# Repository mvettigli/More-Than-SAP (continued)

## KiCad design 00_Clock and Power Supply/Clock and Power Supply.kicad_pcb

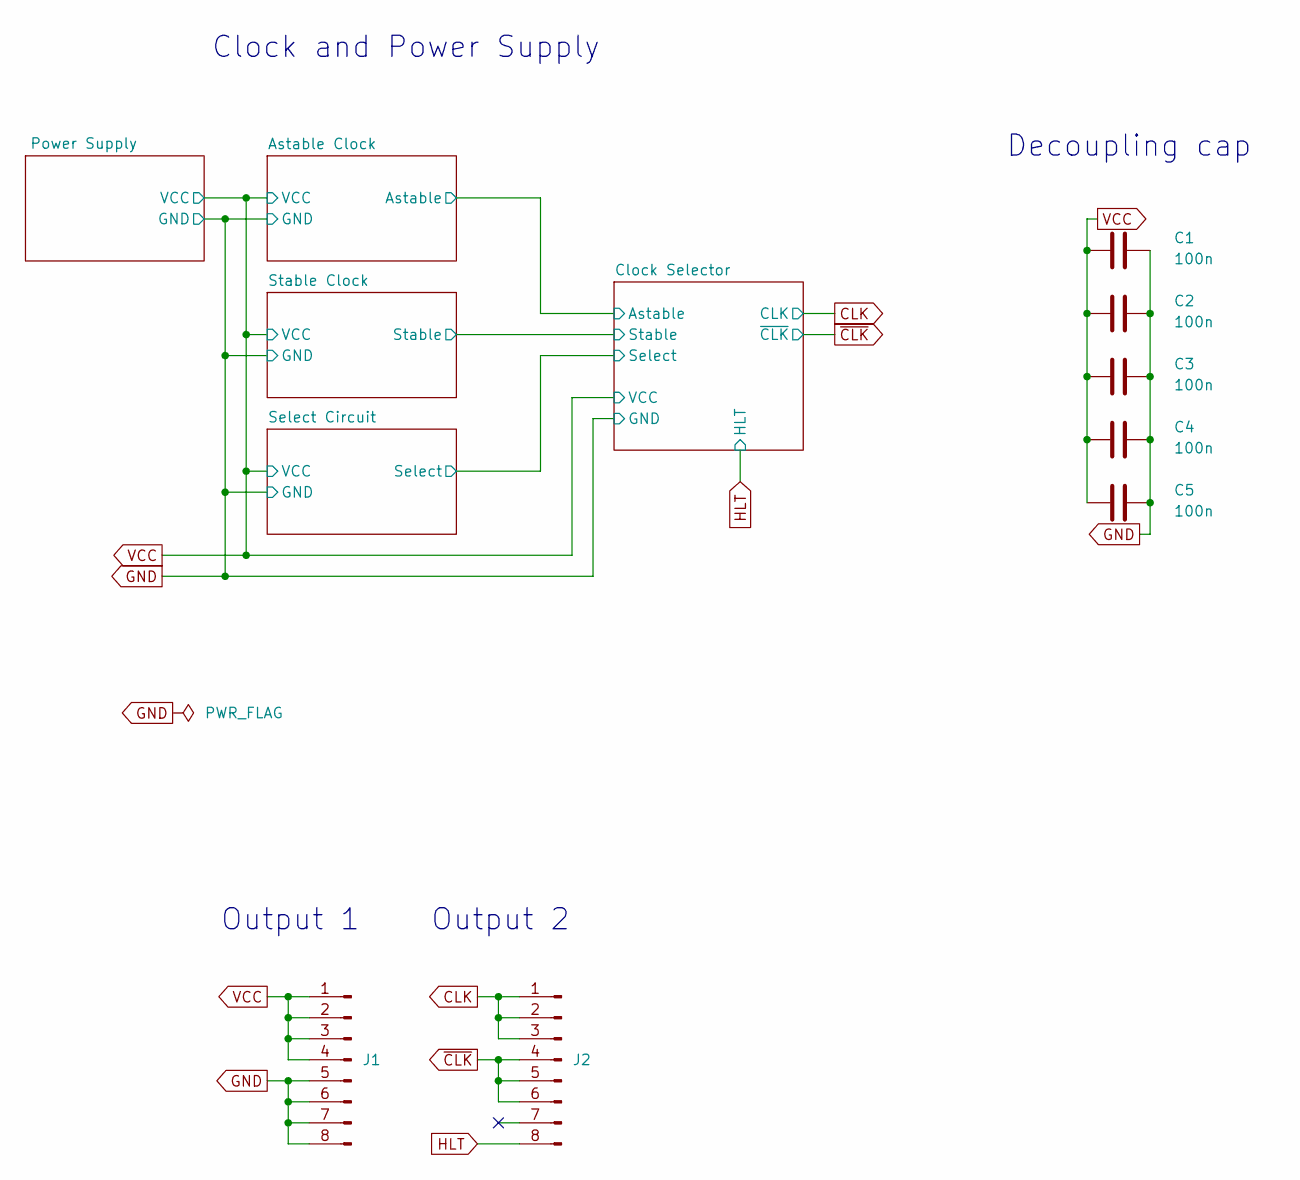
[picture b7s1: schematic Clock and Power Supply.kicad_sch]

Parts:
C1, C2, C3, C4, C5: 100n; C_Disc_D3.0mm_W1.6mm_P2.50mm
J1: Output 1; PinHeader_1x08_P2.54mm_Horizontal
J2: Output 2; PinHeader_1x08_P2.54mm_Horizontal

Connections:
CLK: J2.1, J2.2, J2.3; also elsewhere on the board
GND: C1.2, C2.2, C3.2, C4.2, C5.2, J1.5, J1.6, J1.7, J1.8; also elsewhere on the board
HLT: J2.8; also elsewhere on the board
VCC: C1.1, C2.1, C3.1, C4.1, C5.1, J1.1, J1.2, J1.3, J1.4; also elsewhere on the board
~CLK: J2.4, J2.5, J2.6; also elsewhere on the board

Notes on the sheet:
Clock and Power Supply
Output 2
Output 1
Decoupling cap

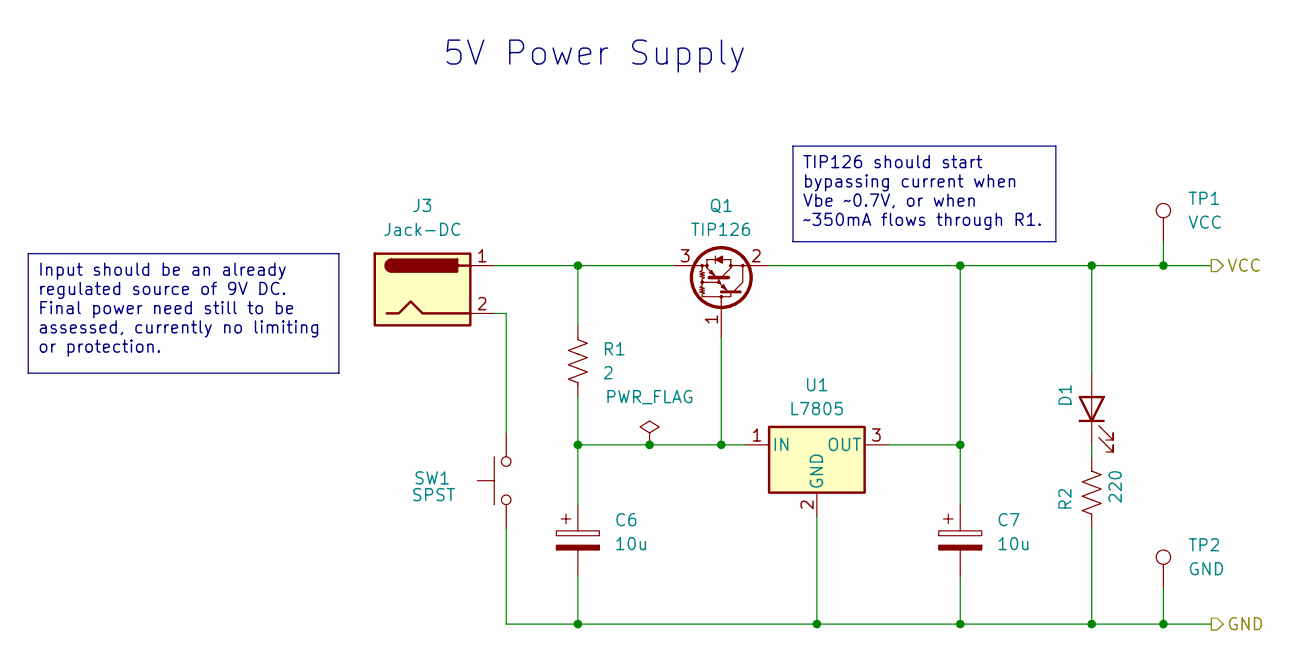
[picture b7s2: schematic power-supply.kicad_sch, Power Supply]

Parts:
C6, C7: 10u; CP_Radial_D5.0mm_P2.50mm
D1: RED; LED_D5.0mm
J3: Jack-DC; BarrelJack_Horizontal
Q1: TIP126; TO-220-3_Vertical
R1: 2; R_Box_L14.0mm_W5.0mm_P9.00mm
R2: 220; R_Axial_DIN0207_L6.3mm_D2.5mm_P10.16mm_Horizontal
SW1: SPST; SW-TH_G-SWITCH-PS-22F03N
TP1: VCC; TestPoint_Loop_D3.50mm_Drill0.9mm_Beaded
TP2: GND; TestPoint_Loop_D3.50mm_Drill0.9mm_Beaded
U1: L7805; TO-220-3_Vertical

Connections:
GND: C6.2, C7.2, R2.2, SW1.1, TP2.1, U1.2 (GND); also elsewhere on the board
unnamed: D1.1 (K), R2.1
unnamed: J3.2, SW1.2
unnamed: C6.1, Q1.1 (B), R1.2, U1.1 (IN)
unnamed: J3.1, Q1.3 (E), R1.1
VCC: C7.1, D1.2 (A), Q1.2 (C), TP1.1, U1.3 (OUT); also elsewhere on the board

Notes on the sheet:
5V Power Supply
TIP126 should start bypassing current when Vbe ~0.7V, or when ~350mA flows through R1.
Input should be an already regulated source of 9V DC. Final power need still to be assessed, currently no limiting or protection.

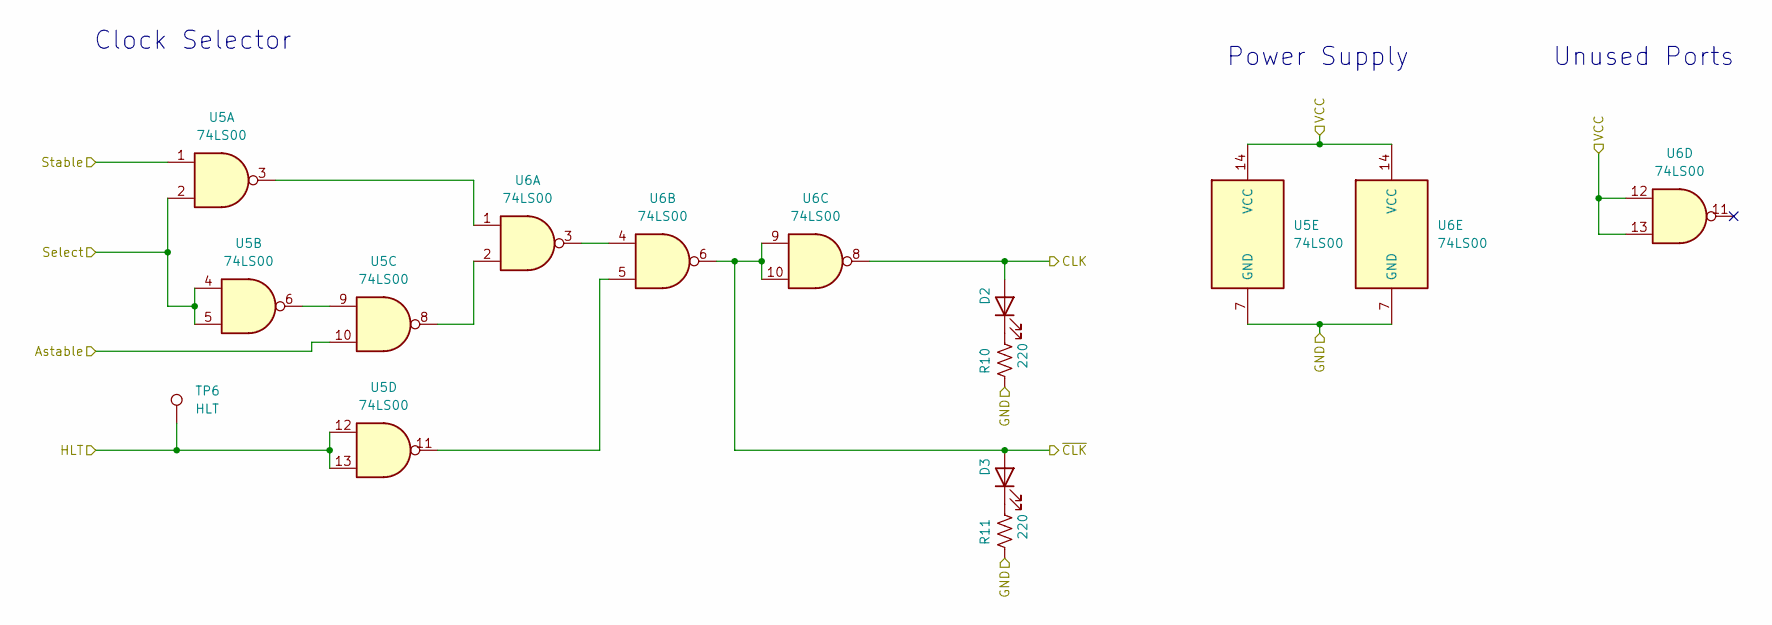
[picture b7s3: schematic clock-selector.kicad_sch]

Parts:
D2, D3: BLUE; LED_D5.0mm
R10, R11: 220; R_Axial_DIN0207_L6.3mm_D2.5mm_P10.16mm_Horizontal
TP6: HLT; TestPoint_Loop_D3.50mm_Drill0.9mm_Beaded
U5, U6: 74LS00; DIP-14_W7.62mm

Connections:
/Astable Clock/Astable: U5.10; also elsewhere on the board
/Clock Selector/Select: U5.2, U5.4, U5.5; also elsewhere on the board
/Clock Selector/Stable: U5.1; also elsewhere on the board
CLK: D2.2 (A), U6.8; also elsewhere on the board
GND: R10.2, R11.2, U5.7 (GND), U6.7 (GND); also elsewhere on the board
HLT: TP6.1, U5.12, U5.13; also elsewhere on the board
unnamed: D2.1 (K), R10.1
unnamed: D3.1 (K), R11.1
unnamed: U5.3, U6.1
unnamed: U5.6, U5.9
unnamed: U5.8, U6.2
unnamed: U5.11, U6.5
unnamed: U6.3, U6.4
VCC: U5.14 (VCC), U6.12, U6.13, U6.14 (VCC); also elsewhere on the board
~CLK: D3.2 (A), U6.6, U6.9, U6.10; also elsewhere on the board

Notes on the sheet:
Power Supply
Unused Ports
Clock Selector

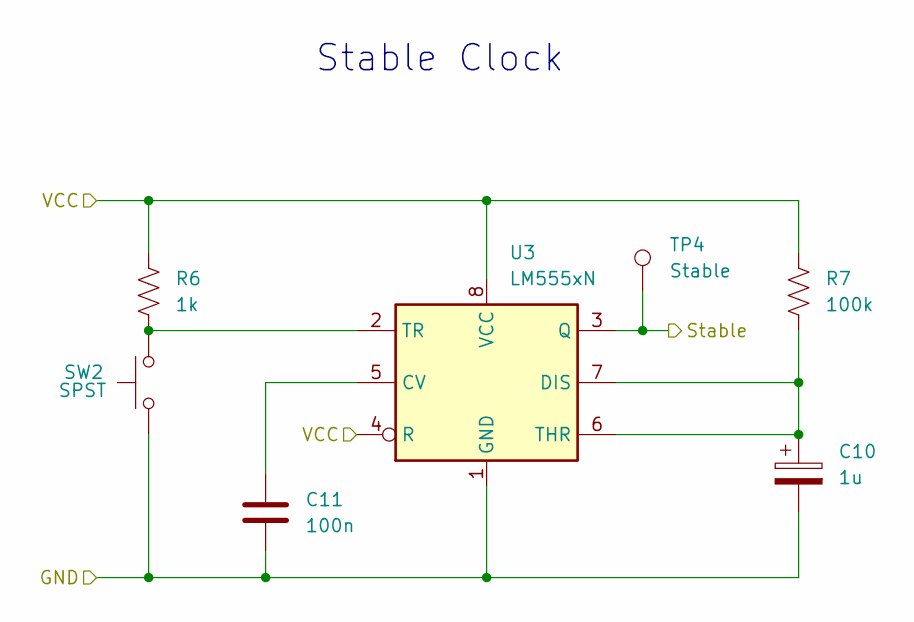
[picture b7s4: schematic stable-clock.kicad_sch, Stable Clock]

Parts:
C10: 1u; CP_Radial_D5.0mm_P2.50mm
C11: 100n; C_Disc_D3.0mm_W1.6mm_P2.50mm
R6: 1k; R_Axial_DIN0207_L6.3mm_D2.5mm_P10.16mm_Horizontal
R7: 100k; R_Axial_DIN0207_L6.3mm_D2.5mm_P10.16mm_Horizontal
SW2: SPST; SW-TH_G-SWITCH-PS-22F03N
TP4: Stable; TestPoint_Loop_D3.50mm_Drill0.9mm_Beaded
U3: LM555xN; DIP-8_W7.62mm

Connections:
/Clock Selector/Stable: TP4.1, U3.3 (Q); also elsewhere on the board
GND: C10.2, C11.2, SW2.1, U3.1 (GND); also elsewhere on the board
unnamed: C11.1, U3.5 (CV)
unnamed: C10.1, R7.1, U3.6 (THR), U3.7 (DIS)
unnamed: R6.1, SW2.2, U3.2 (TR)
VCC: R6.2, R7.2, U3.4 (R), U3.8 (VCC); also elsewhere on the board

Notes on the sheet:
Stable Clock

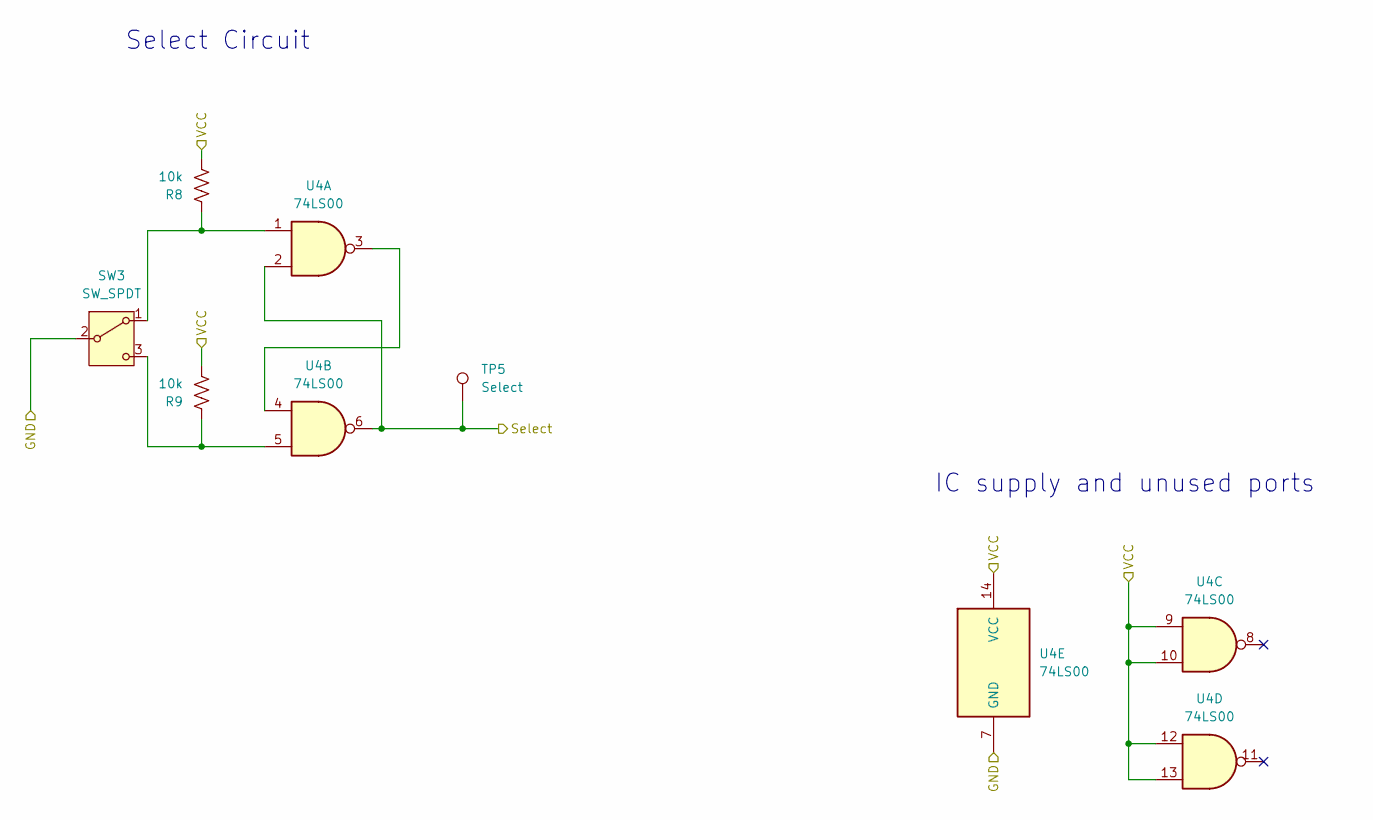
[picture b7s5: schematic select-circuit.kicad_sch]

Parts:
R8, R9: 10k; R_Axial_DIN0207_L6.3mm_D2.5mm_P10.16mm_Horizontal
SW3: SW_SPDT; SW-TH_G-SWITCH-PS-22F03N
TP5: Select; TestPoint_Loop_D3.50mm_Drill0.9mm_Beaded
U4: 74LS00; DIP-14_W7.62mm

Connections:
/Clock Selector/Select: TP5.1, U4.2, U4.6; also elsewhere on the board
GND: SW3.2 (B), U4.7 (GND); also elsewhere on the board
unnamed: R8.1, SW3.1 (A), U4.1
unnamed: R9.1, SW3.3 (C), U4.5
unnamed: U4.3, U4.4
VCC: R8.2, R9.2, U4.9, U4.10, U4.12, U4.13, U4.14 (VCC); also elsewhere on the board

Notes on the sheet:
Select Circuit
IC supply and unused ports

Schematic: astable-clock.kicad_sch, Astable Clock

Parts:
C8: 1u; CP_Radial_D5.0mm_P2.50mm
C9: 100n; C_Disc_D3.0mm_W1.6mm_P2.50mm
R3, R5: 1k; R_Axial_DIN0207_L6.3mm_D2.5mm_P10.16mm_Horizontal
R4: 1M; Potentiometer_Alps_RK09K_Single_Horizontal
TP3: Astable; TestPoint_Loop_D3.50mm_Drill0.9mm_Beaded
U2: LM555xN; DIP-8_W7.62mm

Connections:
/Astable Clock/Astable: TP3.1, U2.3 (Q); also elsewhere on the board
GND: C8.2, C9.2, U2.1 (GND); also elsewhere on the board
unnamed: R4.2, R5.2
unnamed: C9.1, U2.5 (CV)
unnamed: R3.1, R4.1, U2.7 (DIS)
unnamed: C8.1, R5.1, U2.2 (TR), U2.6 (THR)
VCC: R3.2, U2.4 (R), U2.8 (VCC); also elsewhere on the board

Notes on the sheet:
Astable Clock

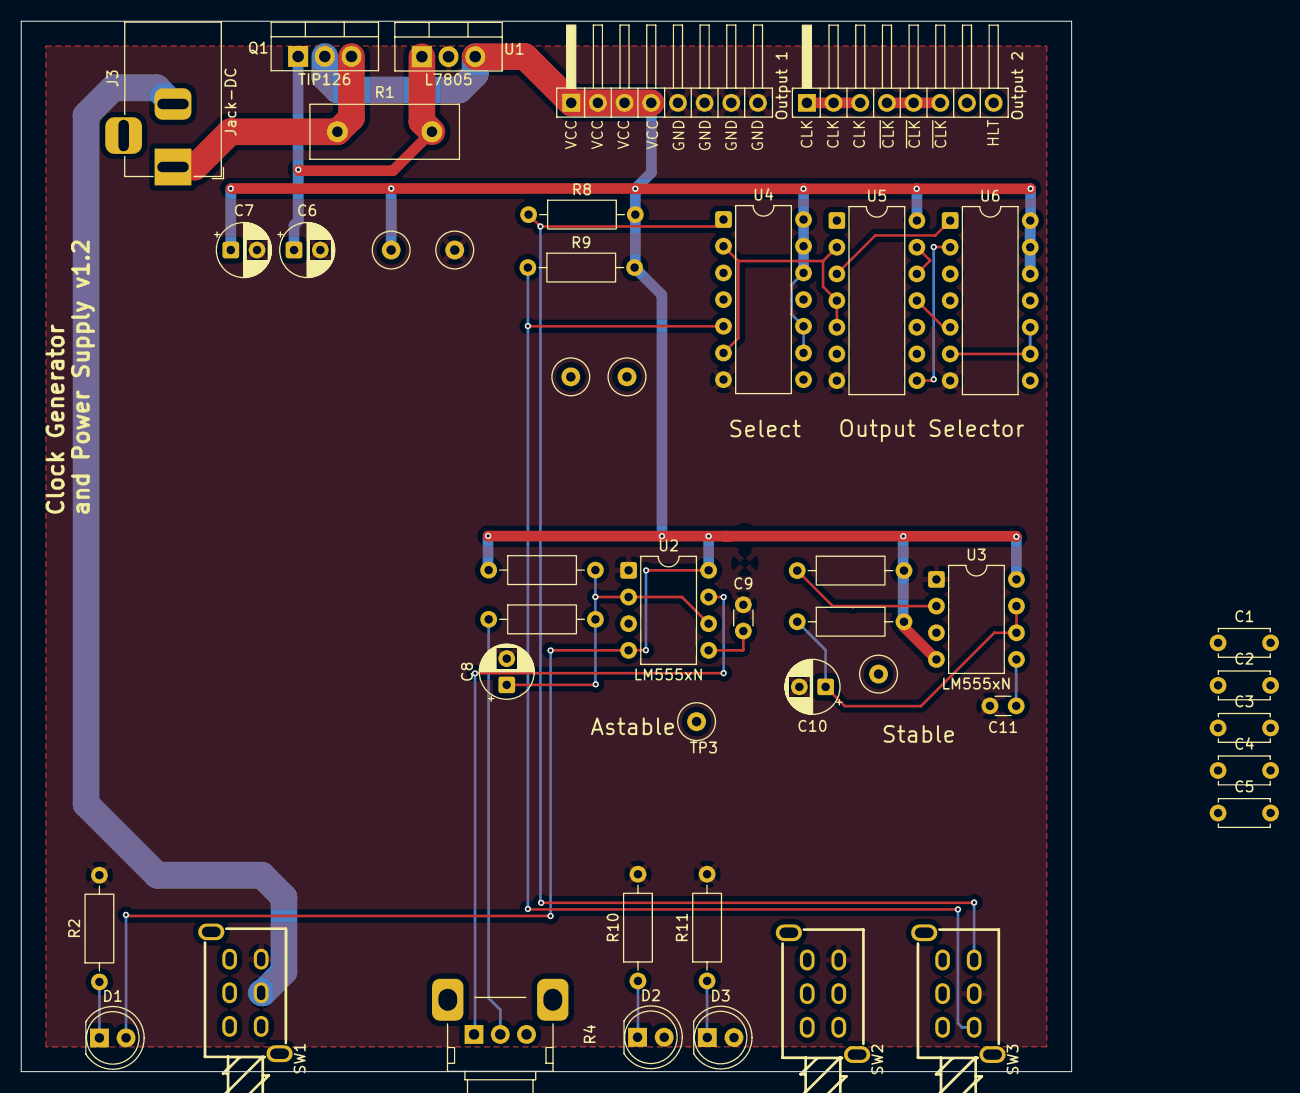
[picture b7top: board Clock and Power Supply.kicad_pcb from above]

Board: 2 copper layers, 100.0 x 100.0 mm, 44 parts (0 on the bottom side), 29 nets.

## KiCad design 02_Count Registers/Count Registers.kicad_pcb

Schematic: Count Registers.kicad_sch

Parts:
C1, C2, C3: 100nF; C_Disc_D4.7mm_W2.5mm_P5.00mm
J1: Data bus; PinHeader_1x08_P2.54mm_Horizontal
J2: Alu-X bus; PinHeader_1x08_P2.54mm_Horizontal
J3: Alu-Y bus; PinHeader_1x08_P2.54mm_Horizontal
J4: Input 1; PinHeader_1x08_P2.54mm_Horizontal
J5: Input 2; PinHeader_1x08_P2.54mm_Horizontal
U1, U3: 74LS08; DIP-14_W7.62mm
U2: 74LS139; DIP-16_W7.62mm

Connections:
/Count register I/U/~D: U1.5, U2.6 (O2); also elsewhere on the board
/Count register I/~CE: U1.6; also elsewhere on the board
/Count register I/~WE: U1.3; also elsewhere on the board
/Count register J/U/~D: U1.10, U2.10 (O2); also elsewhere on the board
/Count register J/~CE: U1.8; also elsewhere on the board
/Count register J/~WE: U1.11; also elsewhere on the board
/Word Selector/~CLR: U3.3; also elsewhere on the board
CLK: J4.2; also elsewhere on the board
D0: J1.1; also elsewhere on the board
D1: J1.2; also elsewhere on the board
D2: J1.3; also elsewhere on the board
D3: J1.4; also elsewhere on the board
D4: J1.5; also elsewhere on the board
D5: J1.6; also elsewhere on the board
D6: J1.7; also elsewhere on the board
D7: J1.8; also elsewhere on the board
GND: C1.2, C2.2, C3.2, J4.8, U1.7 (GND), U2.1 (E), U2.8 (GND), U2.15 (E), U3.4, U3.5, U3.7 (GND), U3.9, U3.10, U3.12, U3.13; also elsewhere on the board
IC0: J4.6, U2.2 (A0)
IC1: J4.7, U2.3 (A1)
JC0: J5.3, U2.14 (A0)
JC1: J5.4, U2.13 (A1)
unnamed: U1.4, U2.5 (O1)
unnamed: U1.2, U2.7 (O3), U3.2
unnamed: U1.9, U2.11 (O1)
unnamed: U1.13, U2.9 (O3), U3.1
VCC: C1.1, C2.1, C3.1, J4.1, U1.14 (VCC), U2.16 (VCC), U3.14 (VCC); also elsewhere on the board
X0: J2.1; also elsewhere on the board
X1: J2.2; also elsewhere on the board
X2: J2.3; also elsewhere on the board
X3: J2.4; also elsewhere on the board
X4: J2.5; also elsewhere on the board
X5: J2.6; also elsewhere on the board
X6: J2.7; also elsewhere on the board
X7: J2.8; also elsewhere on the board
Y0: J3.1; also elsewhere on the board
Y1: J3.2; also elsewhere on the board
Y2: J3.3; also elsewhere on the board
Y3: J3.4; also elsewhere on the board
Y4: J3.5; also elsewhere on the board
Y5: J3.6; also elsewhere on the board
Y6: J3.7; also elsewhere on the board
Y7: J3.8; also elsewhere on the board
~CLK: J4.3
~IRI: J4.5, U1.1
~IRO: J4.4; also elsewhere on the board
~IXO: J5.5; also elsewhere on the board
~IYO: J5.6; also elsewhere on the board
~JRI: J5.2, U1.12
~JRO: J5.1; also elsewhere on the board
~JXO: J5.7; also elsewhere on the board
~JYO: J5.8; also elsewhere on the board

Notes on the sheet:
Alu-X Bus
Data Bus
Input 1
IC Power Supply
Input 2
Decoupling cap
Count Register J
Unsed Ports
ERC
Count Register I
Alu-Y Bus
Two count registers I and J on a same board using the 74LS169 binary counter and 74LS245 for accessing the content to the bus and directly to Alu-X and Alu-Y buses. The up or down clock is selected through 74LS139 decoder and AND ports. A XNOR port should have been used instead of AND but since 2 o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

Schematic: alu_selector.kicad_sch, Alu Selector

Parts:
C10: 10nF; C_Disc_D4.7mm_W2.5mm_P5.00mm
U10: 74LS245; DIP-20_W7.62mm

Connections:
/Alu selector I-X/Q0: U10.2 (A0); also elsewhere on the board
/Alu selector I-X/Q1: U10.3 (A1); also elsewhere on the board
/Alu selector I-X/Q2: U10.4 (A2); also elsewhere on the board
/Alu selector I-X/Q3: U10.5 (A3); also elsewhere on the board
/Alu selector I-X/Q4: U10.6 (A4); also elsewhere on the board
/Alu selector I-X/Q5: U10.7 (A5); also elsewhere on the board
/Alu selector I-X/Q6: U10.8 (A6); also elsewhere on the board
/Alu selector I-X/Q7: U10.9 (A7); also elsewhere on the board
GND: C10.2, U10.10 (GND); also elsewhere on the board
VCC: C10.1, U10.1 (~DIR), U10.20 (VCC); also elsewhere on the board
X0: U10.18 (B0); also elsewhere on the board
X1: U10.17 (B1); also elsewhere on the board
X2: U10.16 (B2); also elsewhere on the board
X3: U10.15 (B3); also elsewhere on the board
X4: U10.14 (B4); also elsewhere on the board
X5: U10.13 (B5); also elsewhere on the board
X6: U10.12 (B6); also elsewhere on the board
X7: U10.11 (B7); also elsewhere on the board
~IXO: U10.19 (~CE); also elsewhere on the board

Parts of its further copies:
C11, C12, C13: 10nF; C_Disc_D4.7mm_W2.5mm_P5.00mm
U11, U12, U13: 74LS245; DIP-20_W7.62mm

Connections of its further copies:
/Alu selector I-X/Q0: U11.2 (A0); also elsewhere on the board
/Alu selector I-X/Q1: U11.3 (A1); also elsewhere on the board
/Alu selector I-X/Q2: U11.4 (A2); also elsewhere on the board
/Alu selector I-X/Q3: U11.5 (A3); also elsewhere on the board
/Alu selector I-X/Q4: U11.6 (A4); also elsewhere on the board
/Alu selector I-X/Q5: U11.7 (A5); also elsewhere on the board
/Alu selector I-X/Q6: U11.8 (A6); also elsewhere on the board
/Alu selector I-X/Q7: U11.9 (A7); also elsewhere on the board
/Alu selector J-X/Q0: U12.2 (A0), U13.2 (A0); also elsewhere on the board
/Alu selector J-X/Q1: U12.3 (A1), U13.3 (A1); also elsewhere on the board
/Alu selector J-X/Q2: U12.4 (A2), U13.4 (A2); also elsewhere on the board
/Alu selector J-X/Q3: U12.5 (A3), U13.5 (A3); also elsewhere on the board
/Alu selector J-X/Q4: U12.6 (A4), U13.6 (A4); also elsewhere on the board
/Alu selector J-X/Q5: U12.7 (A5), U13.7 (A5); also elsewhere on the board
/Alu selector J-X/Q6: U12.8 (A6), U13.8 (A6); also elsewhere on the board
/Alu selector J-X/Q7: U12.9 (A7), U13.9 (A7); also elsewhere on the board
GND: C11.2, C12.2, C13.2, U11.10 (GND), U12.10 (GND), U13.10 (GND); also elsewhere on the board
VCC: C11.1, C12.1, C13.1, U11.1 (~DIR), U11.20 (VCC), U12.1 (~DIR), U12.20 (VCC), U13.1 (~DIR), U13.20 (VCC); also elsewhere on the board
X0: U12.18 (B0); also elsewhere on the board
X1: U12.17 (B1); also elsewhere on the board
X2: U12.16 (B2); also elsewhere on the board
X3: U12.15 (B3); also elsewhere on the board
X4: U12.14 (B4); also elsewhere on the board
X5: U12.13 (B5); also elsewhere on the board
X6: U12.12 (B6); also elsewhere on the board
X7: U12.11 (B7); also elsewhere on the board
Y0: U11.18 (B0), U13.18 (B0); also elsewhere on the board
Y1: U11.17 (B1), U13.17 (B1); also elsewhere on the board
Y2: U11.16 (B2), U13.16 (B2); also elsewhere on the board
Y3: U11.15 (B3), U13.15 (B3); also elsewhere on the board
Y4: U11.14 (B4), U13.14 (B4); also elsewhere on the board
Y5: U11.13 (B5), U13.13 (B5); also elsewhere on the board
Y6: U11.12 (B6), U13.12 (B6); also elsewhere on the board
Y7: U11.11 (B7), U13.11 (B7); also elsewhere on the board
~IYO: U11.19 (~CE); also elsewhere on the board
~JXO: U12.19 (~CE); also elsewhere on the board
~JYO: U13.19 (~CE); also elsewhere on the board

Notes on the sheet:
Decoupling cap

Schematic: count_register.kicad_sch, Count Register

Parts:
C4, C5, C6: 10nF; C_Disc_D4.7mm_W2.5mm_P5.00mm
D1, D2, D3, D4, D5, D6, D7, D8: RED; LED_D3.0mm
R1, R2, R3, R4, R5, R6, R7, R8: 220; R_Axial_DIN0207_L6.3mm_D2.5mm_P10.16mm_Horizontal
U4, U6: 74LS169; DIP-16_W7.62mm
U5: 74LS245; DIP-20_W7.62mm

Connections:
/Alu selector I-X/Q0: D1.2 (A), U4.14 (Q0), U5.2 (A0); also elsewhere on the board
/Alu selector I-X/Q1: D2.2 (A), U4.13 (Q1), U5.3 (A1); also elsewhere on the board
/Alu selector I-X/Q2: D3.2 (A), U4.12 (Q2), U5.4 (A2); also elsewhere on the board
/Alu selector I-X/Q3: D4.2 (A), U4.11 (Q3), U5.5 (A3); also elsewhere on the board
/Alu selector I-X/Q4: D5.2 (A), U5.6 (A4), U6.14 (Q0); also elsewhere on the board
/Alu selector I-X/Q5: D6.2 (A), U5.7 (A5), U6.13 (Q1); also elsewhere on the board
/Alu selector I-X/Q6: D7.2 (A), U5.8 (A6), U6.12 (Q2); also elsewhere on the board
/Alu selector I-X/Q7: D8.2 (A), U5.9 (A7), U6.11 (Q3); also elsewhere on the board
/Count register I/U/~D: U4.1 (U/~D), U6.1 (U/~D); also elsewhere on the board
/Count register I/~CE: U4.7 (~CEP), U6.7 (~CEP); also elsewhere on the board
/Count register I/~WE: U4.9 (~PE), U6.9 (~PE); also elsewhere on the board
CLK: U4.2 (CP), U6.2 (CP); also elsewhere on the board
GND: C4.2, C5.2, C6.2, R1.2, R2.2, R3.2, R4.2, R5.2, R6.2, R7.2, R8.2, U4.8 (GND), U4.10 (~CET), U5.10 (GND), U6.8 (GND); also elsewhere on the board
unnamed: D1.1 (K), R1.1
unnamed: D2.1 (K), R2.1
unnamed: D3.1 (K), R3.1
unnamed: D4.1 (K), R4.1
unnamed: D5.1 (K), R5.1
unnamed: D6.1 (K), R6.1
unnamed: D7.1 (K), R7.1
unnamed: D8.1 (K), R8.1
unnamed: U4.15 (~TC), U6.10 (~CET)
S0: U4.3 (P0), U5.18 (B0); also elsewhere on the board
S1: U4.4 (P1), U5.17 (B1); also elsewhere on the board
S2: U4.5 (P2), U5.16 (B2); also elsewhere on the board
S3: U4.6 (P3), U5.15 (B3); also elsewhere on the board
S4: U5.14 (B4), U6.3 (P0); also elsewhere on the board
S5: U5.13 (B5), U6.4 (P1); also elsewhere on the board
S6: U5.12 (B6), U6.5 (P2); also elsewhere on the board
S7: U5.11 (B7), U6.6 (P3); also elsewhere on the board
VCC: C4.1, C5.1, C6.1, U4.16 (VCC), U5.1 (~DIR), U5.20 (VCC), U6.16 (VCC); also elsewhere on the board
~IRO: U5.19 (~CE); also elsewhere on the board

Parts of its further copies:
C7, C8, C9: 10nF; C_Disc_D4.7mm_W2.5mm_P5.00mm
D9, D10, D11, D12, D13, D14, D15, D16: RED; LED_D3.0mm
R9, R10, R11, R12, R13, R14, R15, R16: 220; R_Axial_DIN0207_L6.3mm_D2.5mm_P10.16mm_Horizontal
U7, U9: 74LS169; DIP-16_W7.62mm
U8: 74LS245; DIP-20_W7.62mm

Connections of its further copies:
/Alu selector J-X/Q0: D9.2 (A), U7.14 (Q0), U8.2 (A0); also elsewhere on the board
/Alu selector J-X/Q1: D10.2 (A), U7.13 (Q1), U8.3 (A1); also elsewhere on the board
/Alu selector J-X/Q2: D11.2 (A), U7.12 (Q2), U8.4 (A2); also elsewhere on the board
/Alu selector J-X/Q3: D12.2 (A), U7.11 (Q3), U8.5 (A3); also elsewhere on the board
/Alu selector J-X/Q4: D13.2 (A), U8.6 (A4), U9.14 (Q0); also elsewhere on the board
/Alu selector J-X/Q5: D14.2 (A), U8.7 (A5), U9.13 (Q1); also elsewhere on the board
/Alu selector J-X/Q6: D15.2 (A), U8.8 (A6), U9.12 (Q2); also elsewhere on the board
/Alu selector J-X/Q7: D16.2 (A), U8.9 (A7), U9.11 (Q3); also elsewhere on the board
/Count register J/U/~D: U7.1 (U/~D), U9.1 (U/~D); also elsewhere on the board
/Count register J/~CE: U7.7 (~CEP), U9.7 (~CEP); also elsewhere on the board
/Count register J/~WE: U7.9 (~PE), U9.9 (~PE); also elsewhere on the board
CLK: U7.2 (CP), U9.2 (CP); also elsewhere on the board
GND: C7.2, C8.2, C9.2, R9.2, R10.2, R11.2, R12.2, R13.2, R14.2, R15.2, R16.2, U7.8 (GND), U7.10 (~CET), U8.10 (GND), U9.8 (GND); also elsewhere on the board
unnamed: D9.1 (K), R9.1
unnamed: D10.1 (K), R10.1
unnamed: D11.1 (K), R11.1
unnamed: D12.1 (K), R12.1
unnamed: D13.1 (K), R13.1
unnamed: D14.1 (K), R14.1
unnamed: D15.1 (K), R15.1
unnamed: D16.1 (K), R16.1
unnamed: U7.15 (~TC), U9.10 (~CET)
S0: U7.3 (P0), U8.18 (B0); also elsewhere on the board
S1: U7.4 (P1), U8.17 (B1); also elsewhere on the board
S2: U7.5 (P2), U8.16 (B2); also elsewhere on the board
S3: U7.6 (P3), U8.15 (B3); also elsewhere on the board
S4: U8.14 (B4), U9.3 (P0); also elsewhere on the board
S5: U8.13 (B5), U9.4 (P1); also elsewhere on the board
S6: U8.12 (B6), U9.5 (P2); also elsewhere on the board
S7: U8.11 (B7), U9.6 (P3); also elsewhere on the board
VCC: C7.1, C8.1, C9.1, U7.16 (VCC), U8.1 (~DIR), U8.20 (VCC), U9.16 (VCC); also elsewhere on the board
~JRO: U8.19 (~CE); also elsewhere on the board

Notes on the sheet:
Decoupling cap
Out driver
Count Register
Data bus or null word is switched thanks to 74LS157 quad 2-1 line multiplexer. The control bit is ~{CLR}. The word is pushed syncronously on the counter register 74LS169 with ~{WE}. Up/down counter is enabled with ~{CE} and selected with U/~{D} pin.

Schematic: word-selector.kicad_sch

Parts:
C14, C15: 10nF; C_Disc_D4.7mm_W2.5mm_P5.00mm
U14, U15: 74LS157; DIP-16_W7.62mm

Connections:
/Word Selector/~CLR: U14.1 (S), U15.1 (S); also elsewhere on the board
D0: U14.3 (I1a); also elsewhere on the board
D1: U14.6 (I1b); also elsewhere on the board
D2: U14.10 (I1c); also elsewhere on the board
D3: U14.13 (I1d); also elsewhere on the board
D4: U15.3 (I1a); also elsewhere on the board
D5: U15.6 (I1b); also elsewhere on the board
D6: U15.10 (I1c); also elsewhere on the board
D7: U15.13 (I1d); also elsewhere on the board
GND: C14.2, C15.2, U14.2 (I0a), U14.5 (I0b), U14.8 (GND), U14.11 (I0c), U14.14 (I0d), U14.15 (E), U15.2 (I0a), U15.5 (I0b), U15.8 (GND), U15.11 (I0c), U15.14 (I0d), U15.15 (E); also elsewhere on the board
S0: U14.4 (Za); also elsewhere on the board
S1: U14.7 (Zb); also elsewhere on the board
S2: U14.9 (Zc); also elsewhere on the board
S3: U14.12 (Zd); also elsewhere on the board
S4: U15.4 (Za); also elsewhere on the board
S5: U15.7 (Zb); also elsewhere on the board
S6: U15.9 (Zc); also elsewhere on the board
S7: U15.12 (Zd); also elsewhere on the board
VCC: C14.1, C15.1, U14.16 (VCC), U15.16 (VCC); also elsewhere on the board

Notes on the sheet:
Decoupling cap

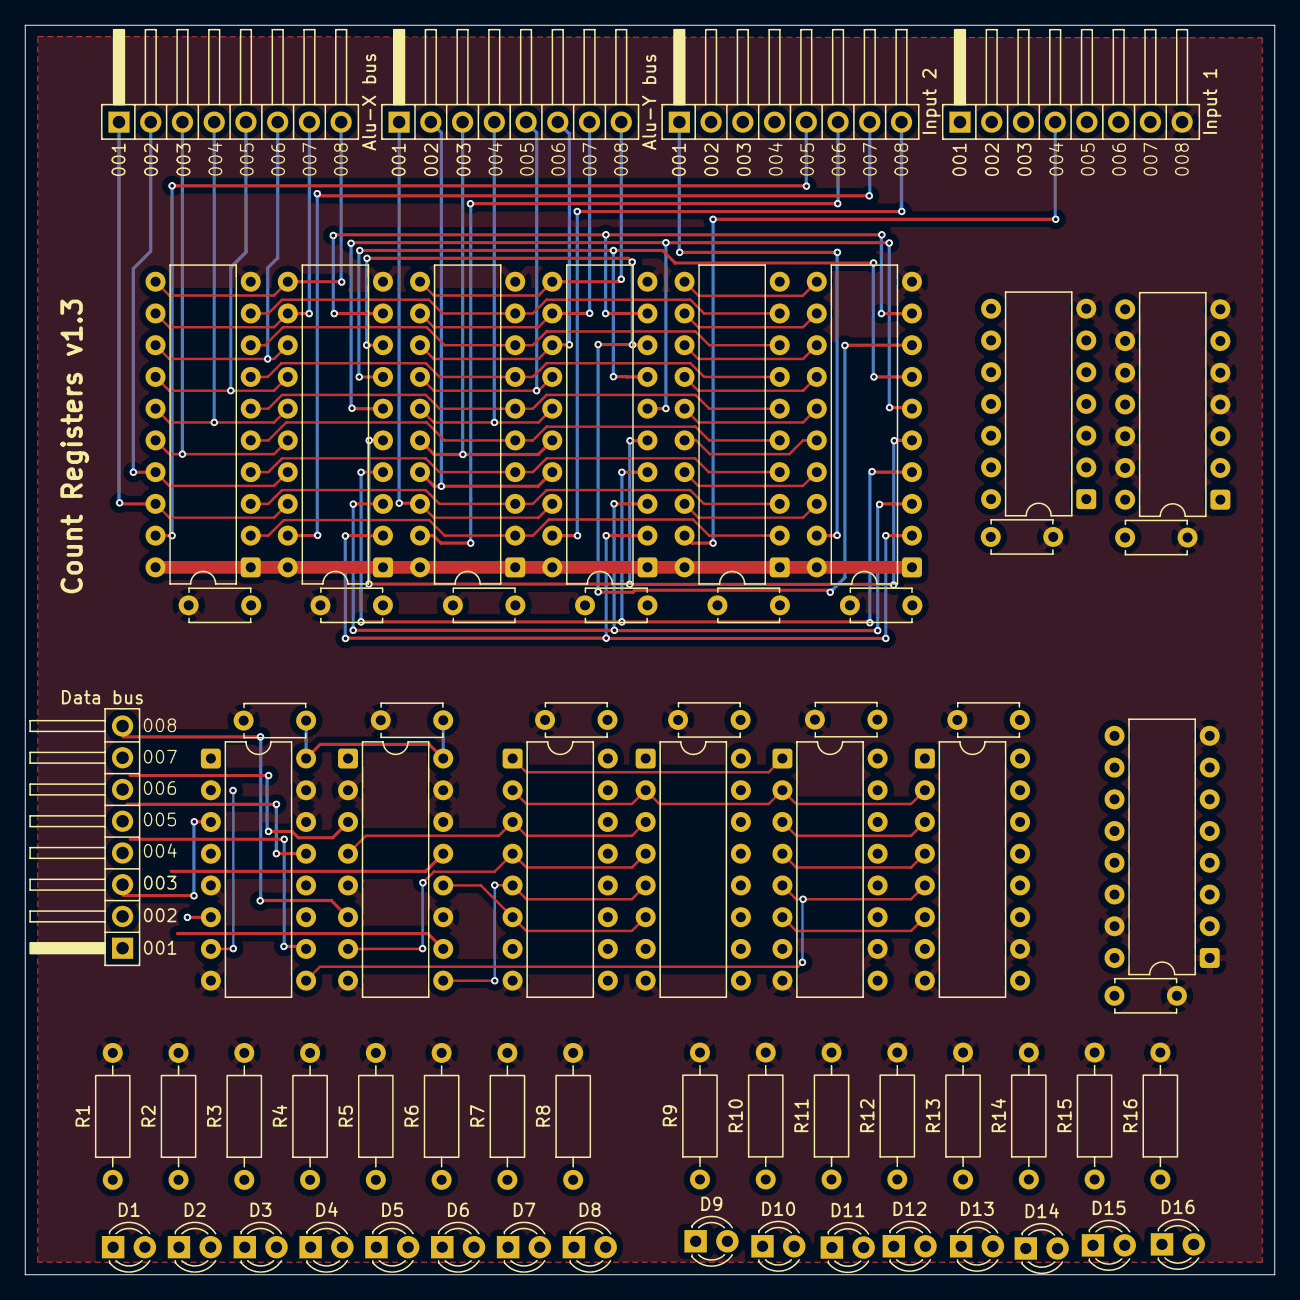
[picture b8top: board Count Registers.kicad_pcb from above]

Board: 2 copper layers, 100.0 x 100.0 mm, 67 parts (0 on the bottom side), 92 nets.

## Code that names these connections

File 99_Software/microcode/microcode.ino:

#define SHIFT_DATA 2
#define SHIFT_CLK 3
#define SHIFT_LATCH 4
#define EEPROM_D0 5
#define EEPROM_D7 12
#define WRITE_ENABLE 13

void setAddress(int address, bool outputEnable) {
  // Shift 16-bit address, 8 bits at a time
  byte firstBits = (address >> 8) | (outputEnable ? 0x00 : 0x80);
  byte lastBits = address;
  shiftOut(SHIFT_DATA, SHIFT_CLK, MSBFIRST, firstBits);
  shiftOut(SHIFT_DATA, SHIFT_CLK, MSBFIRST, lastBits);

  // Latch the data with one clock pulse
  digitalWrite(SHIFT_LATCH, LOW);
  digitalWrite(SHIFT_LATCH, HIGH);
  digitalWrite(SHIFT_LATCH, LOW);
}

byte readEEPROM(int address) {
  // Set all data pins as input
  for (int pin = EEPROM_D0; pin <= EEPROM_D7; pin++) {
    pinMode(pin, INPUT);
  }

  setAddress(address, true);  // Enable output

  byte data = 0;
  // Read from D7 to D0 (MSB first)
  for (int pin = EEPROM_D7; pin >= EEPROM_D0; pin--) {
    data = (data << 1) + digitalRead(pin);
  }
  return data;
}

void writeEEPROM(int address, byte data) {
  // Set all data pins as output
  for (int pin = EEPROM_D0; pin <= EEPROM_D7; pin++) {
    pinMode(pin, OUTPUT);
  }

  setAddress(address, false);  // Disable output for writing

  // Write data bits (D0 = LSB, D7 = MSB)
  for (int pin = EEPROM_D0; pin <= EEPROM_D7; pin++) {
    digitalWrite(pin, data & 1);
    data = data >> 1;
  }

  // Write enable pulse
  digitalWrite(WRITE_ENABLE, LOW);
  delayMicroseconds(1);
  digitalWrite(WRITE_ENABLE, HIGH);
  delay(10);  // Write cycle time
}

void eraseEEPROM(int size) {
  Serial.print("Erasing EEPROM...");
  for (int address = 0; address < size; address++) {
    writeEEPROM(address, 0xff);
    if (address % 64 == 0) {
      Serial.print(".");  // Progress indicator
    }
  }
  Serial.println(" Done!");
}

// Fixed function signature and logic
void programBytes(byte data[], int dataSize) {
  Serial.print("Programming EEPROM...");
  for (int address = 0; address < dataSize; address++) {
    writeEEPROM(address, data[address]);
    if (address % 64 == 0) {
      Serial.print(".");  // Progress indicator
    }
  }
  Serial.println(" Done!");
}

void printContents(int size) {
  Serial.println("EEPROM Contents:");
  // Loop through 16-byte rows
  for (int base = 0; base < size; base += 16) {
    byte data[16];

    // Read 16 bytes (or remaining bytes if less than 16)
    int bytesToRead = min(16, size - base);
    for (int offset = 0; offset < bytesToRead; offset++) {
      data[offset] = readEEPROM(base + offset);
    }

    // Format and print hex dump
    char buf[80];
    sprintf(buf, "%04x: %02x %02x %02x %02x %02x %02x %02x %02x   %02x %02x %02x %02x %02x %02x %02x %02x",
            base, data[0], data[1], data[2], data[3], data[4], data[5], data[6], data[7],
            data[8], data[9], data[10], data[11], data[12], data[13], data[14], data[15]);
    
    Serial.println(buf);
 
  }

}

// Utility function to verify written data
bool verifyEEPROM(byte data[], int dataSize) {
  Serial.print("Verifying EEPROM...");
  for (int address = 0; address < dataSize; address++) {
    byte readValue = readEEPROM(address);
    if (readValue != data[address]) {
      Serial.println();
      Serial.print("Verification failed at address 0x");
      Serial.print(address, HEX);
      Serial.print(": expected 0x");
      Serial.print(data[address], HEX);
      Serial.print(", got 0x");
      Serial.println(readValue, HEX);
      return false;
    }
    if (address % 64 == 0) {
      Serial.print(".");
    }
  }
  Serial.println(" Passed!");
  return true;
}

void setup() {
  // Initialize shift register pins
  pinMode(SHIFT_DATA, OUTPUT);
  pinMode(SHIFT_CLK, OUTPUT);
  pinMode(SHIFT_LATCH, OUTPUT);

  // Initialize write enable pin (active LOW)
  digitalWrite(WRITE_ENABLE, HIGH);  // Disable writes initially
  pinMode(WRITE_ENABLE, OUTPUT);

  // Initialize serial communication
  Serial.begin(57600);
  Serial.println("EEPROM Programmer Ready");
  Serial.println("========================");

  // Erase the EEPROM
  //eraseEEPROM(2048);

  // Display current contents
  printContents(2048);

  // Example: Program some test data
  /*
    byte testData[] = {0xAA, 0x55, 0xFF, 0x00, 0x12, 0x34, 0x56, 0x78};
    int testSize = sizeof(testData);

    programBytes(testData, testSize);
    verifyEEPROM(testData, testSize);
    printContents(16);  // Show first 16 bytes
  */
}

// 1** Alu Operation ---
// 00: OC0 = Alu code 0
// 01: OC1 = Alu code 1
// 02: OC2 = Alu code 2
// 03: OC3 = Alu code 3
// --- Register file ---
// 04: XC0 = X code 0
// 05: XC1 = X code 1
// 06: YC0 = Y code 0
// 07: YC1 = Y code 1
// 2** Data bus out code ---
// 08: DC0 = Data bus out code 0
// 09: DC1 = Data bus out code 1
// 10: DC2 = Data bus out code 2
// 11: DC3 = Data bus out code 3
// --- Address out code ---
// 12: AC0 = Address out code 0
// 13: AC1 = Address out code 1
// 14: AC2 = Address out code 2
// 15: AC3 = Address out code 3
// 3** Shift registers ---
// 16: LC0 = Shift register L code 0
// 17: LC1 = Shift register L code 1
// 18: RC0 = Shift register L code 0
// 19: RC1 = Shift register L code 1
// --- Count registers ---
// 20: IC0 = Count register I code 0
// 21: IC1 = Count register I code 1
// 22: JC0 = Count register J code 0
// 23: JC1 = Count register J code 1
// 4** Data in code ---
// 24: BC0 = Data bus in code 0
// 25: BC1 = Data bus in code 1
// 26: BC2 = Data bus in code 2
// 27: BC3 = Data bus in code 3
// --- Stack Pointer & MAR ---
// 28: SC0 = Stack pointer code 0
// 29: SC1 = Stack pointer code 1
// 30: MC0 = MAR code 0
// 31: MC1 = MAR code 1
// 5** Others ---
// 32: PCE = Program Counter Enable (0 = disable, 1 = enable)
// 33: FLS = Flag Register Select (0 = ALU, 1 = Bus)
// 34: PCR = Program Counter Reset (1 = disable, 0 = enable)
// 35: SSR = Step Sequencer Reset (1 = disable, 0 = enable)
// 36: HLT = Halt (1 = disable, 0 = enable)
// 37: RST = Reset (1 = disable, 0 = enable)
// 38: Unused
// 39: Unused

#define ADD 0b_00000000_00000000_00000000_00000000_00000000_00000000
#define SUB 0b_00000001_00000000_00000000_00000000_00000000_00000000
#define AND 0b_00000010_00000000_00000000_00000000_00000000_00000000
#define OR  0b_00000011_00000000_00000000_00000000_00000000_00000000
#define XOR 0b_00000100_00000000_00000000_00000000_00000000_00000000



void loop() {
  // Main loop - could add serial command interface here
}

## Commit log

2025-12-05 Alu control and modules completed, as well as Stack pointer module
2026-01-04 Last revision of the cpu, all boards have been ordered. Implementation to be tested and documented in following commits.
2026-01-04 Clean up of backup folders.
2026-01-04 Instruction register v1.11 Corrected label ~{SSR} to SSR, no modification to the circuit itself. Active low and high inputs swapped from Input2 to Input1.
2026-01-10 Update 10-01-2026 - Fixed bug on program counter - Fist ISA review, still in draft - Added missing mounting holes on memory modules
